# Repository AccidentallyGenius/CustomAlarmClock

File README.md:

# CustomAlarmClock
A custom pyramidal-shaped alarm clock with a 2x3 key matrix and a 2.25-inch TFT display. A software layer uses the keys and screen to let the user play a game where they must press the keys in the correct order to stop the alarm from ringing.

# CAD Model:

# Schematic Diagram:

# PCB:

# Bill of Materials (BoM):
- 6x Cherry MX Switches
- 6x DSA Keycaps
- 6x 1N4148 DO-35 Diodes.
- 8x M3x5x4 Heatset inserts
- 4x M3x16mm Screws
- 4x M3x8mm Screws
- 1x XIAO RP2040
- 1x Case (2 printed parts)
- 1x PCB
- 1x 2.25in TFT Screen
- 1x 3.3V Piezo Buzzer
- 1x 2.54mm 8 Pin Male Header
- 8x 20cm Female-Female Jumper Wires

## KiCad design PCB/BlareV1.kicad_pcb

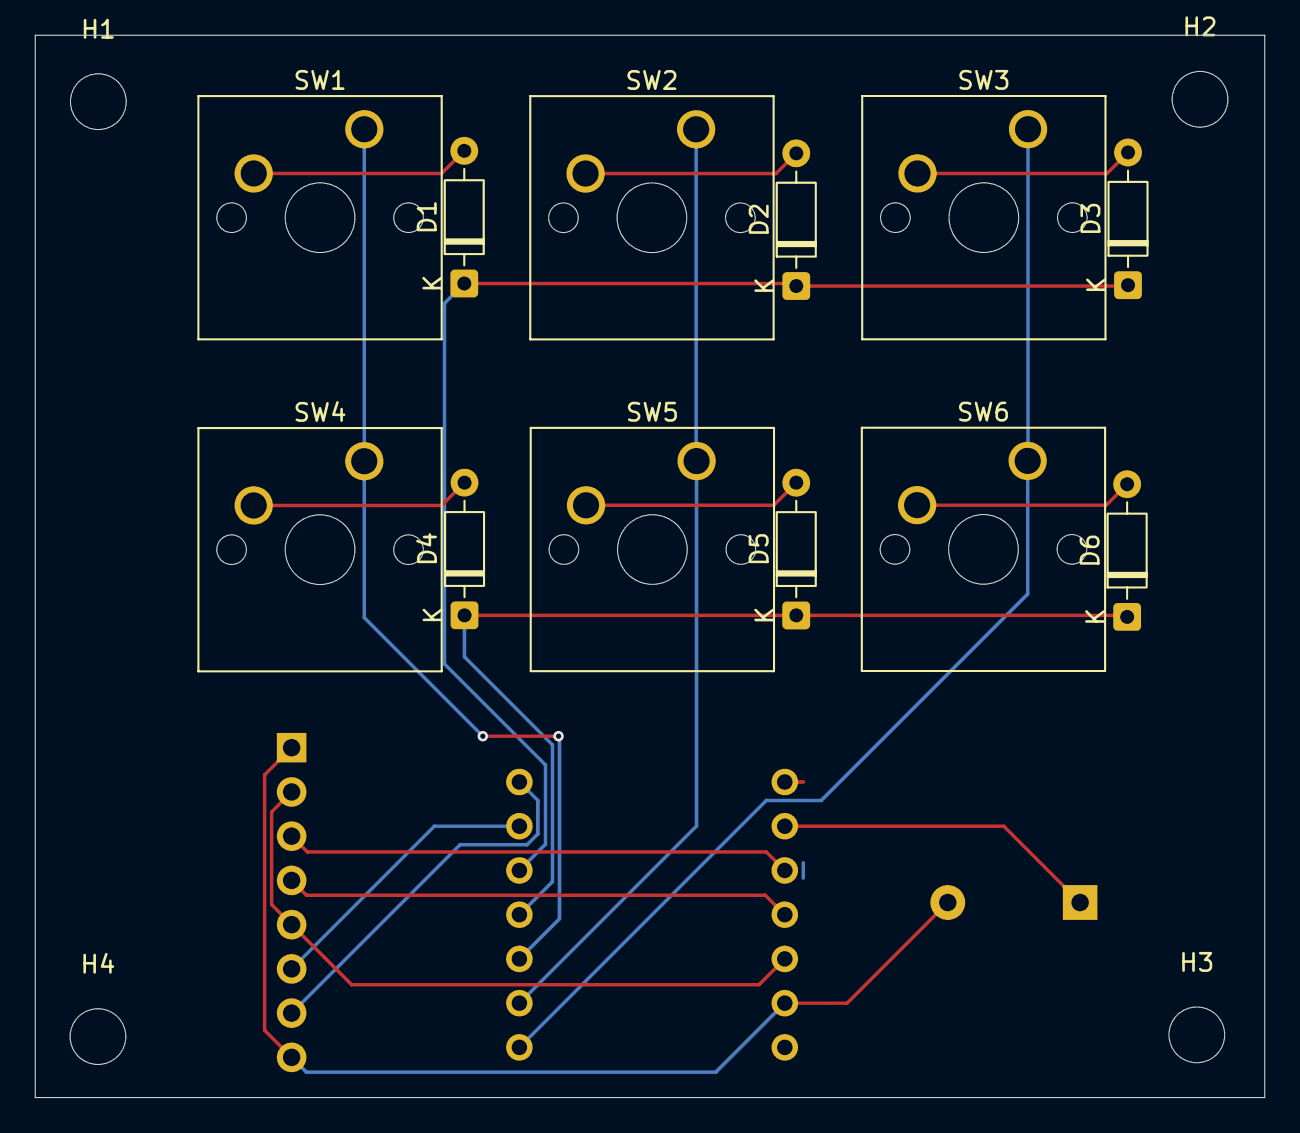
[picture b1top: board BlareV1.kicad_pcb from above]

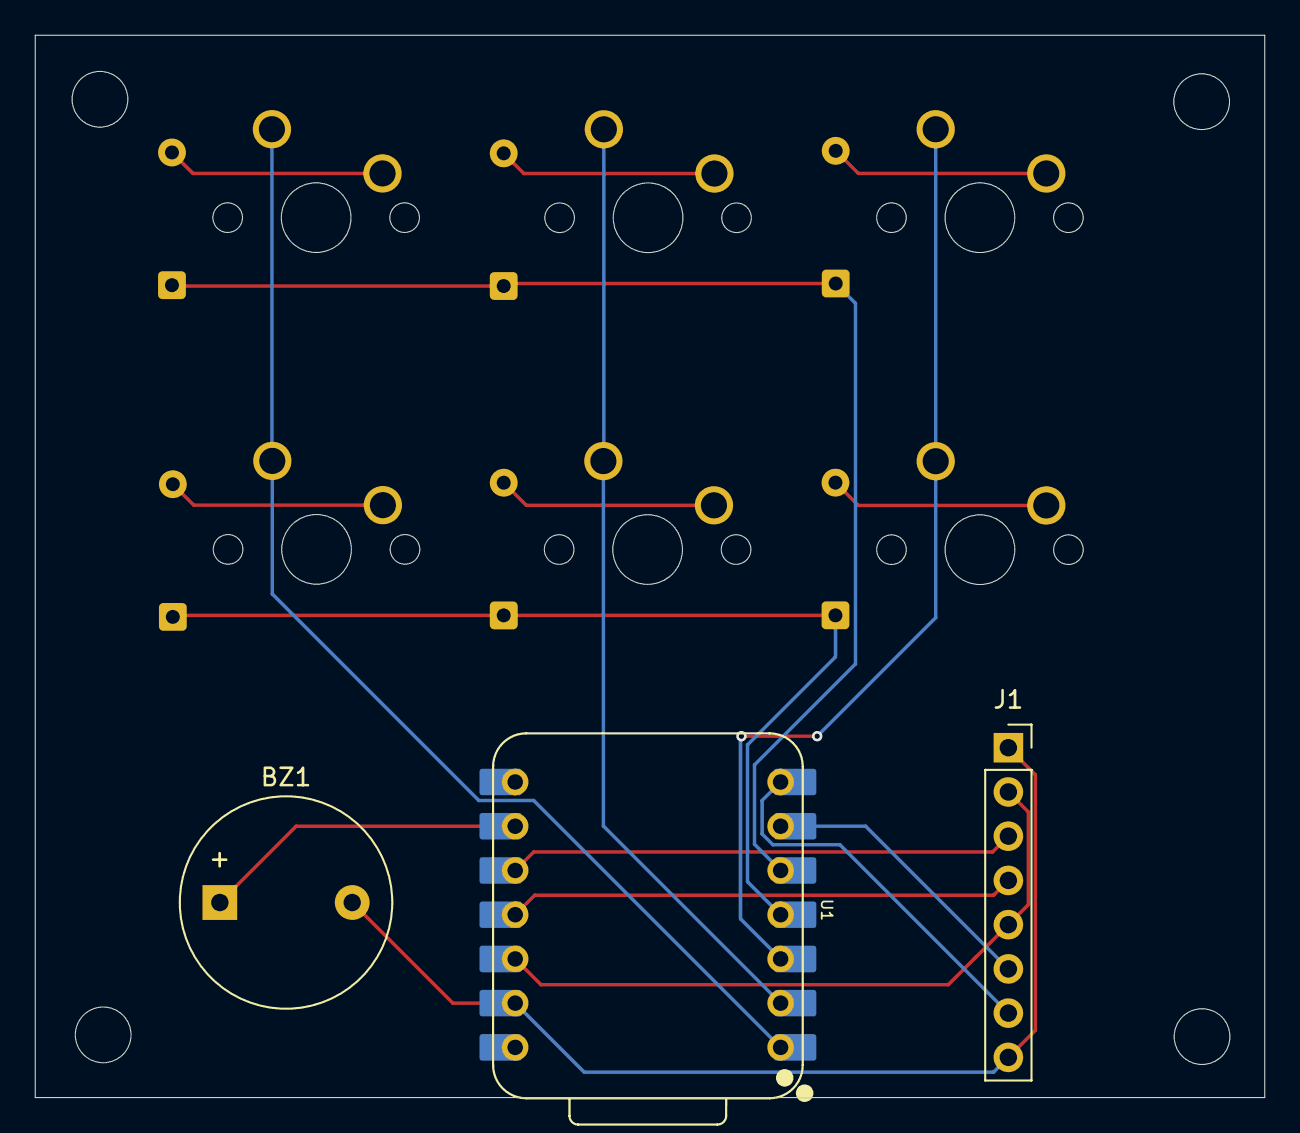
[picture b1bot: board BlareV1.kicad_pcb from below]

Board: 2 copper layers, 70.6 x 61.0 mm, 19 parts (3 on the bottom side), 18 nets.

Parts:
BZ1: Buzzer; Buzzer_12x9.5RM7.6
D1, D2, D3, D4, D5, D6: 1N4148; D_DO-35_SOD27_P7.62mm_Horizontal
H1, H2, H3, H4: MountingHole; MountingHole_3.2mm_M3
J1: Conn_01x08_Pin; PinSocket_1x08_P2.54mm_Vertical
SW1, SW2, SW3, SW4, SW5, SW6: SW_Push; SW_Cherry_MX_1.00u_PCB
U1: XIAO-ESP32-C3-SMD; XIAO-ESP32-C3-DIP

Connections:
+3.3V: J1.2, J1.5, U1.12 (3V3_OUT)
/Buzzer_1: BZ1.1 (+), U1.9 (D8)
/CS: J1.7, U1.7 (D6)
/Column_0: SW1.1, SW4.1, U1.3 (D2)
/Column_1: SW2.1, SW5.1, U1.2 (D1)
/Column_2: SW3.1, SW6.1, U1.1 (D0)
/DC: J1.6, U1.6 (D5)
/Row_0: D1.1 (K), D2.1 (K), D3.1 (K), U1.5 (D4)
/Row_1: D4.1 (K), D5.1 (K), D6.1 (K), U1.4 (D3)
/SCL: J1.3, U1.10 (D9/BOOT)
/SDA: J1.4, U1.11 (D10)
GND: BZ1.2 (-), J1.1, J1.8, U1.13 (GND)
unnamed: D1.2 (A), SW1.2
unnamed: D2.2 (A), SW2.2
unnamed: D3.2 (A), SW3.2
unnamed: D4.2 (A), SW4.2
unnamed: D5.2 (A), SW5.2
unnamed: D6.2 (A), SW6.2
